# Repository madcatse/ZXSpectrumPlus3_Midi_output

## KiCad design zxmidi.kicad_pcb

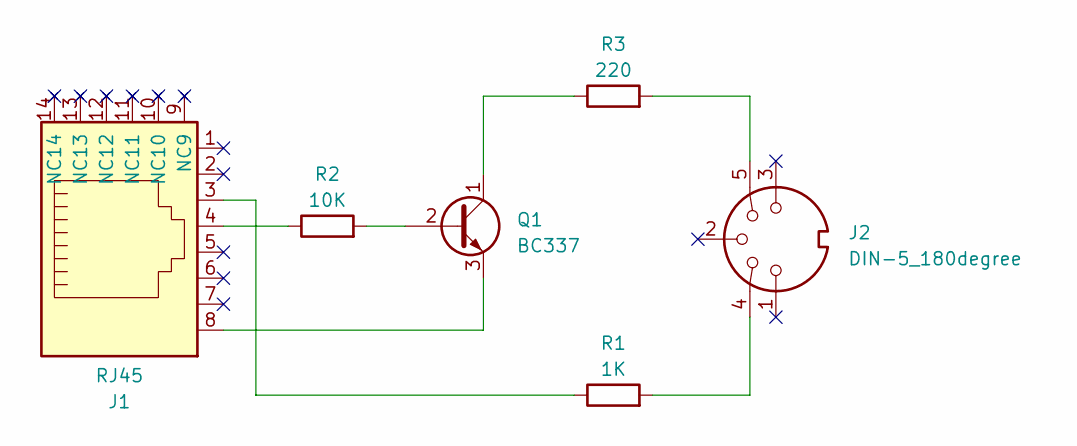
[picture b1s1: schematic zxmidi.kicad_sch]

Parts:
J1: RJ45; RJ45_Amphenol_54602-x08_Horizontal
J2: DIN-5_180degree; din-5
Q1: BC337; TO-92_Inline
R1: 1K; R_Axial_DIN0207_L6.3mm_D2.5mm_P10.16mm_Horizontal
R2: 10K; R_Axial_DIN0207_L6.3mm_D2.5mm_P10.16mm_Horizontal
R3: 220; R_Axial_DIN0207_L6.3mm_D2.5mm_P10.16mm_Horizontal

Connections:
unnamed: J1.3, R1.1
unnamed: J1.4, R2.1
unnamed: J2.4, R1.2
unnamed: J2.5, R3.2
unnamed: Q1.2 (B), R2.2
unnamed: Q1.1 (C), R3.1
unnamed: J1.8, Q1.3 (E)

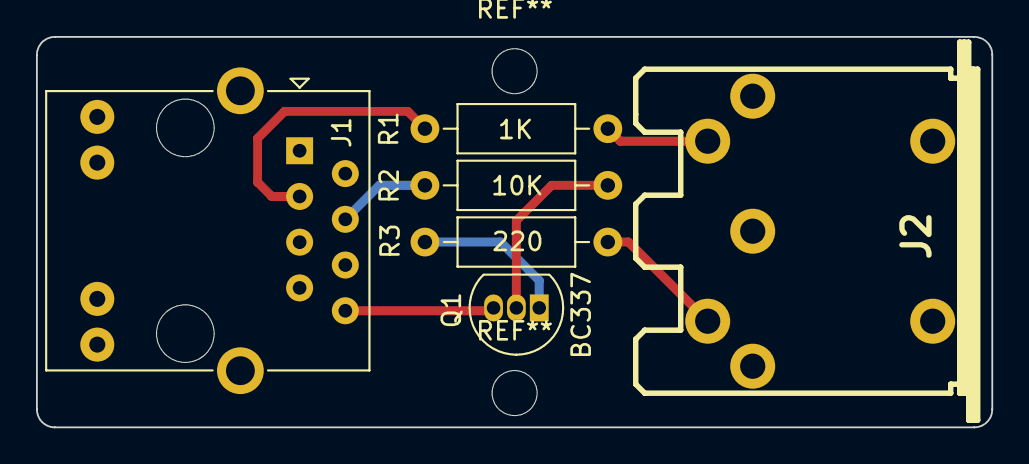
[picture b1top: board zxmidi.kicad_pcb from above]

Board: 2 copper layers, 53.1 x 21.7 mm, 6 parts (0 on the bottom side), 7 nets.

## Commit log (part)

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2023-04-20 Initial
2023-04-21 Gerbers
2023-09-22 3d models rework
2025-01-02 Error fix
2025-01-03 Case draft
2025-01-28 Gerbers fixed
